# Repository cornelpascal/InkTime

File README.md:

# InkTime

- Cerinta proiectului: https://ocw.cs.pub.ro/courses/tsc/proiect2026
- Portalul de piese JLC mentionat in brief: https://jlcpcb.com/parts

Repository-ul contine schema electrica, PCB-ul, fisierele de manufacturing si ansamblul mecanic pentru un wearable bazat pe nRF52840, cu Bluetooth Low Energy, incarcare prin USB-C, interfata pentru display e-paper, motion sensing, haptic feedback si monitorizare baterie.

## Continutul Repository-ului

- `Hardware/`
  - `WatchSchematic.sch` - schema nativa
  - `WatchSchematic.brd` - layout PCB nativ
  - `WatchSchematic.pdf` / `WatchSchematic1.pdf` - exporturi PDF ale schemei
- `Manufacturing/`
  - `Gerbers.zip` - exporturi Gerber, drill si assembly
  - `bom.csv` - export BOM pentru manufacturing
  - `pick_and_place_top.cpl` - date de plasare pentru fata top
  - `pick_and_place_bottom.cpl` - date de plasare pentru fata bottom
- `Mechanical/`
  - `WatchMechanical.f3z` - assembly Fusion 360
  - `WatchMechanical.step` - export CAD neutru
- `Images/`
  - capturi de render pentru PCB/dispozitiv

## Diagrama Bloc

```text
                         +----------------------+
USB-C -----------------> | USB ESD Protection   |
                         +----------+-----------+
                                    |
                                    v
                         +----------------------+
                         | BQ25180 Charger/PMIC |
                         +----+------------+----+
                              |            |
                              |            +--------------------+
                              v                                 |
                       +-------------+                          |
                       | Li-Po       |                          |
                       | Battery     | --------------------+   |
                       +------+------+                     |   |
                              |                            v   v
                              |                  +----------------------+
                              +----------------> | MAX17048 Fuel Gauge  |
                                                 +----------------------+

                         +----------------------+
                         | RT6160A Buck-Boost   |
                         | 3.3 V Regulator      |
                         +----+----+----+-------+
                              |    |    |
                              |    |    +---------------------> Display E-Paper pe FPC 24 pini
                              |    |
                              |    +-------------------------> DRV2605 Haptic Driver ---> Motor vibratii
                              |
                              +------------------------------> BMA423 IMU
                              |
                              v
                    +-----------------------------------+
                    | nRF52840 BLE + USB MCU            |
                    |                                   |
                    | I2C  -> PMIC / Fuel / IMU / Haptic|
                    | SPI  -> Display E-Paper           |
                    | GPIO -> Butoane / INT / EN        |
                    | USB  -> D+ / D-                   |
                    | SWD  -> Debug Tag-Connect         |
                    +-----+-----------+--------+--------+
                          |           |        |
                          |           |        +--------> Tag-Connect SWD
                          |           +-----------------> 3 butoane user
                          +-----------------------------> Matching Network -> Antena 2.4 GHz
```

## Prezentare Hardware

### Arhitectura principala

- `nRF52840` este controlerul principal. A fost ales deoarece combina BLE, USB, suficienti GPIO, moduri low-power si un ecosistem RF intr-un singur pachet.
- Alimentarea intra prin `USB-C`, trece prin protectia ESD si este gestionata de `BQ25180YBGR`, un charger / PMIC pentru o singura celula.
- Linia de alimentare sustinuta de baterie este reglata de `RT6160AWSC`, un convertor buck-boost care genereaza rail-ul principal `3V3` indiferent de variatia tensiunii bateriei.
- Starea bateriei este masurata de `MAX17048G+T10`.
- Motion sensing este oferit de `BMA423`.
- Haptic feedback este generat de `DRV2605YZFR`, controlat prin I2C si activat printr-un GPIO dedicat.
- Display-ul este conectat printr-un conector `FPC 24 pini, 0.5 mm` si foloseste o magistrala dedicata de tip SPI plus linii de reset/busy/control.
- Semnalul RF de la nRF52840 trece printr-o retea discreta de matching catre o antena chip de 2.4 GHz plasata pe marginea PCB-ului.

### Decizii de design vizibile in implementare

- Toate componentele populate sunt plasate pe fata top; fisierul pick-and-place pentru bottom este gol, conform ghidajului din cerinta.
- Antena RF este pastrata pe marginea placii si separata de zonele dense de cupru, ceea ce respecta cerinta proiectului privind clearance-ul antenei.
- Ceasul foloseste trei butoane hardware pe GPIO-uri dedicate in loc sa le multiplexeze prin display sau PMIC.

## Bill of Materials

BOM-ul complet exportat pentru manufacturing este in [`Manufacturing/bom.csv`](Manufacturing/bom.csv). Tabelul de mai jos listeaza componentele functionale principale, iar coloana `JLC Parts` foloseste fie linkul exact extras din proiect, fie portalul JLC Parts pentru cautarea manuala dupa MPN atunci cand codul JLC nu apare explicit in export.

| Ref | Part | Rol | JLC Parts | Datasheet |
| --- | --- | --- | --- | --- |
| `U1` | nRF52840 | MCU principal BLE/USB | https://jlcpcb.com/partdetail/JLCPCBAssembly-nRF52840/C9900031370 | https://www.nordicsemi.com/-/media/Software-and-other-downloads/Product-Briefs/nRF52840-product-brief.pdf |
| `IC1` | BQ25180YBGR | Charger / PMIC pentru o singura celula | https://jlcpcb.com/partdetail/TexasInstruments-BQ25180YBGR/C3682423 | https://www.ti.com/lit/ds/symlink/bq25180.pdf |
| `IC9` | RT6160AWSC | Regulator buck-boost 3.3 V | https://jlcpcb.com/partdetail/C7065276 | https://www.richtek.com/assets/product_file/RT6160A=RTQ2520A/DS6160A-05.pdf |
| `U3` | MAX17048G+T10 | Fuel gauge pentru baterie | https://jlcpcb.com/partdetail/MaximIntegrated-MAX17048GT10/C2682616 | https://www.analog.com/media/en/technical-documentation/data-sheets/MAX17048-MAX17049.pdf |
| `IC2` | DRV2605YZFR | Driver haptic | https://jlcpcb.com/partdetail/TexasInstruments-DRV2605YZFR/C81079 | https://www.ti.com/lit/ds/symlink/drv2605.pdf |
| `L7` | FTC252012SR47MBCA | Inductor pentru buck-boost | https://jlcpcb.com/partdetail/6763488-FTC252012SR47MBCA/C5832368 | https://product.tdk.com/system/files/dam/doc/product/inductor/inductor/smd/catalog/inductor_commercial_power_mlp2016_en.pdf |
| `IC3` | BMA423 | Accelerometru pe 3 axe | https://jlcpcb.com/parts | https://www.bosch-sensortec.com/media/boschsensortec/downloads/datasheets/bst-bma423-ds000.pdf |
| `ANT1` | 2450AT18B100E | Antena chip 2.4 GHz | https://jlcpcb.com/parts | https://www.johansontechnology.com/datasheets/2450AT18B100.pdf |
| `J1` | Molex 503480-2400 | Conector FPC 24 pini pentru display | https://jlcpcb.com/parts | https://www.molex.com/pdm_docs/sd/5034802400_sd.pdf |
| `J2` | TC2030-IDC | Conector de programare Tag-Connect | https://jlcpcb.com/parts | https://www.tag-connect.com/wp-content/uploads/bsk-pdf-manager/TC2030-IDC-NL.pdf |
| `J4` | KH-TYPE-C-16P | Receptacul USB-C | https://jlcpcb.com/parts | https://atta.szlcsc.com/upload/public/pdf/source/20230720/8A9E0F0B650D1A2FD53D4D542E2F6B37.pdf |
| `D3` | USBLC6-2SC6Y | Protectie ESD pentru USB | https://jlcpcb.com/parts | https://www.st.com/resource/en/datasheet/usblc6-2.pdf |
| `SW_UP`, `SW_ENT`, `SW_DN` | Panasonic EVP-AKE31A | Butoane user | https://jlcpcb.com/parts | https://industry.panasonic.com/cdbs/www-data/pdf/ASQ0000/ASQ0000CE50.pdf |

## Alocare Pini nRF52840

Tabelul urmator documenteaza alocarile efective observate in schema pentru `U1` (`nRF52840`).

| Pin nRF52840 | Net / semnal | Utilizare in design |
| --- | --- | --- |
| `P0.00` | `XL1` | Terminal cristal LF 32.768 kHz |
| `P0.01` | `XL2` | Terminal cristal LF 32.768 kHz |
| `P0.02` | `SCK` | SPI clock pentru display-ul e-paper |
| `P0.03` | `MOSI` | SPI MOSI pentru display-ul e-paper |
| `P0.05` | `EPD_CS` | Chip select pentru display |
| `P0.06` | `SDA` | I2C SDA comun pentru PMIC, fuel gauge, haptic si alte periferice I2C |
| `P0.07` | `SCL` | I2C SCL comun pentru PMIC, fuel gauge, haptic si alte periferice I2C |
| `P0.08` | `IMU_INT1` | Intrerupere principala de la `BMA423` |
| `P0.10` | `ALERT` | Semnal `ALERT` de la `MAX17048` |
| `P0.11` | `PMIC_INT` | Intrerupere de la `BQ25180` |
| `P0.12` | `HAPTIC_EN` | Enable pentru `DRV2605` |
| `P0.13` | `P0.13` | Intrare buton `SW_UP` |
| `P0.14` | `P0.14` | Intrare buton `SW_ENT` |
| `P0.15` | `EPD_DC` | Linia data/command pentru display |
| `P0.16` | `EPD_RST` | Reset hardware pentru display |
| `P0.17` | `EPD_BUSY` | Busy/status de la display |
| `P0.18` | `RESET` | Reset extern, dus si la Tag-Connect (`J2`) |
| `P1.00` | `SWO` | Optional trace / debug output pe test pad |
| `P1.02` | `P1.02` | Intrare buton `SW_DN` |
| `P1.08` | `IMU_INT2` | A doua intrerupere de la `BMA423` |
| `SWDIO` | `SWDIO` | Debug/programare prin `J2` |
| `SWDCLK` | `SWDCLK` | Clock debug/programare prin `J2` |
| `D-` | `D-` | USB FS data minus de la conectorul USB-C, prin protectia ESD |
| `D+` | `D+` | USB FS data plus de la conectorul USB-C, prin protectia ESD |
| `VBUS` | `VBUS` | Detectie/alimentare USB venita din conectorul USB-C |

Pinii `P0.04`, `P0.09`, `P1.01`, `P1.03`-`P1.07`, `P1.09`-`P1.15` si `P0.19`-`P0.31` apar in simbolul MCU, dar in schema curenta nu au o functie periferica documentata explicit; pot ramane disponibili pentru extensii sau pentru iteratii viitoare ale designului.

## Fisiere de Manufacturing

Artefactele prezente in acest repository:

- Arhiva Gerber: [`Manufacturing/Gerbers.zip`](Manufacturing/Gerbers.zip)
- Datele de drill incluse in arhiva
- Fisiere de assembly placement:
  - [`Manufacturing/pick_and_place_top.cpl`](Manufacturing/pick_and_place_top.cpl)
  - [`Manufacturing/pick_and_place_bottom.cpl`](Manufacturing/pick_and_place_bottom.cpl)
- Export BOM: [`Manufacturing/bom.csv`](Manufacturing/bom.csv)

Arhiva Gerber curenta contine fisiere pentru top/bottom copper, soldermask, silkscreen, solderpaste, drill si profile. Fisierul de plasare pentru top este populat; fisierul de plasare pentru bottom este gol, ceea ce este consistent cu o strategie de asamblare doar pe fata top.

## Livrabile Mecanice

- Ansamblu Fusion: [`Mechanical/WatchMechanical.f3z`](Mechanical/WatchMechanical.f3z)
- Export STEP: [`Mechanical/WatchMechanical.step`](Mechanical/WatchMechanical.step)

Aceste fisiere sunt destinate validarii potrivirii carcasei pentru PCB, baterie, stack-ul display-ului si alinierea conectorilor/butoanelor ceruta de proiect.

## Imagini Render

## Note de Implementare

- Designul urmeaza structura ceruta de proiect pentru `Hardware`, `Manufacturing`, `Mechanical`, `Images`, `LICENSE` si `README.md`.
- PCB-ul este o placa compacta pentru wearable, cu functii RF, power, sensing, haptics, display, USB si debug integrate intr-un singur design.
- Arhitectura aleasa minimizeaza modulele externe prin integrarea directa pe placa a functiilor de charging, regulation, sensing, battery monitoring si control haptic.
- Zonele cele mai sensibile la rutare sunt traseul RF, regiunea perechii diferentiale USB, zona de conversie de putere si sectiunea densa a conectorului de display.

## Aliniere cu Checklist-ul de Review

Acest README a fost scris pentru a acoperi documentatia necesara:

- diagrama bloc
- BOM cu linkuri de procurement si datasheet
- functionalitate hardware detaliata
- utilizarea explicita a pinilor nRF52840
- note de implementare utile in timpul review-ului
- linkuri catre schema, PCB-ul, fisierele de manufacturing si artefactele mecanice livrate

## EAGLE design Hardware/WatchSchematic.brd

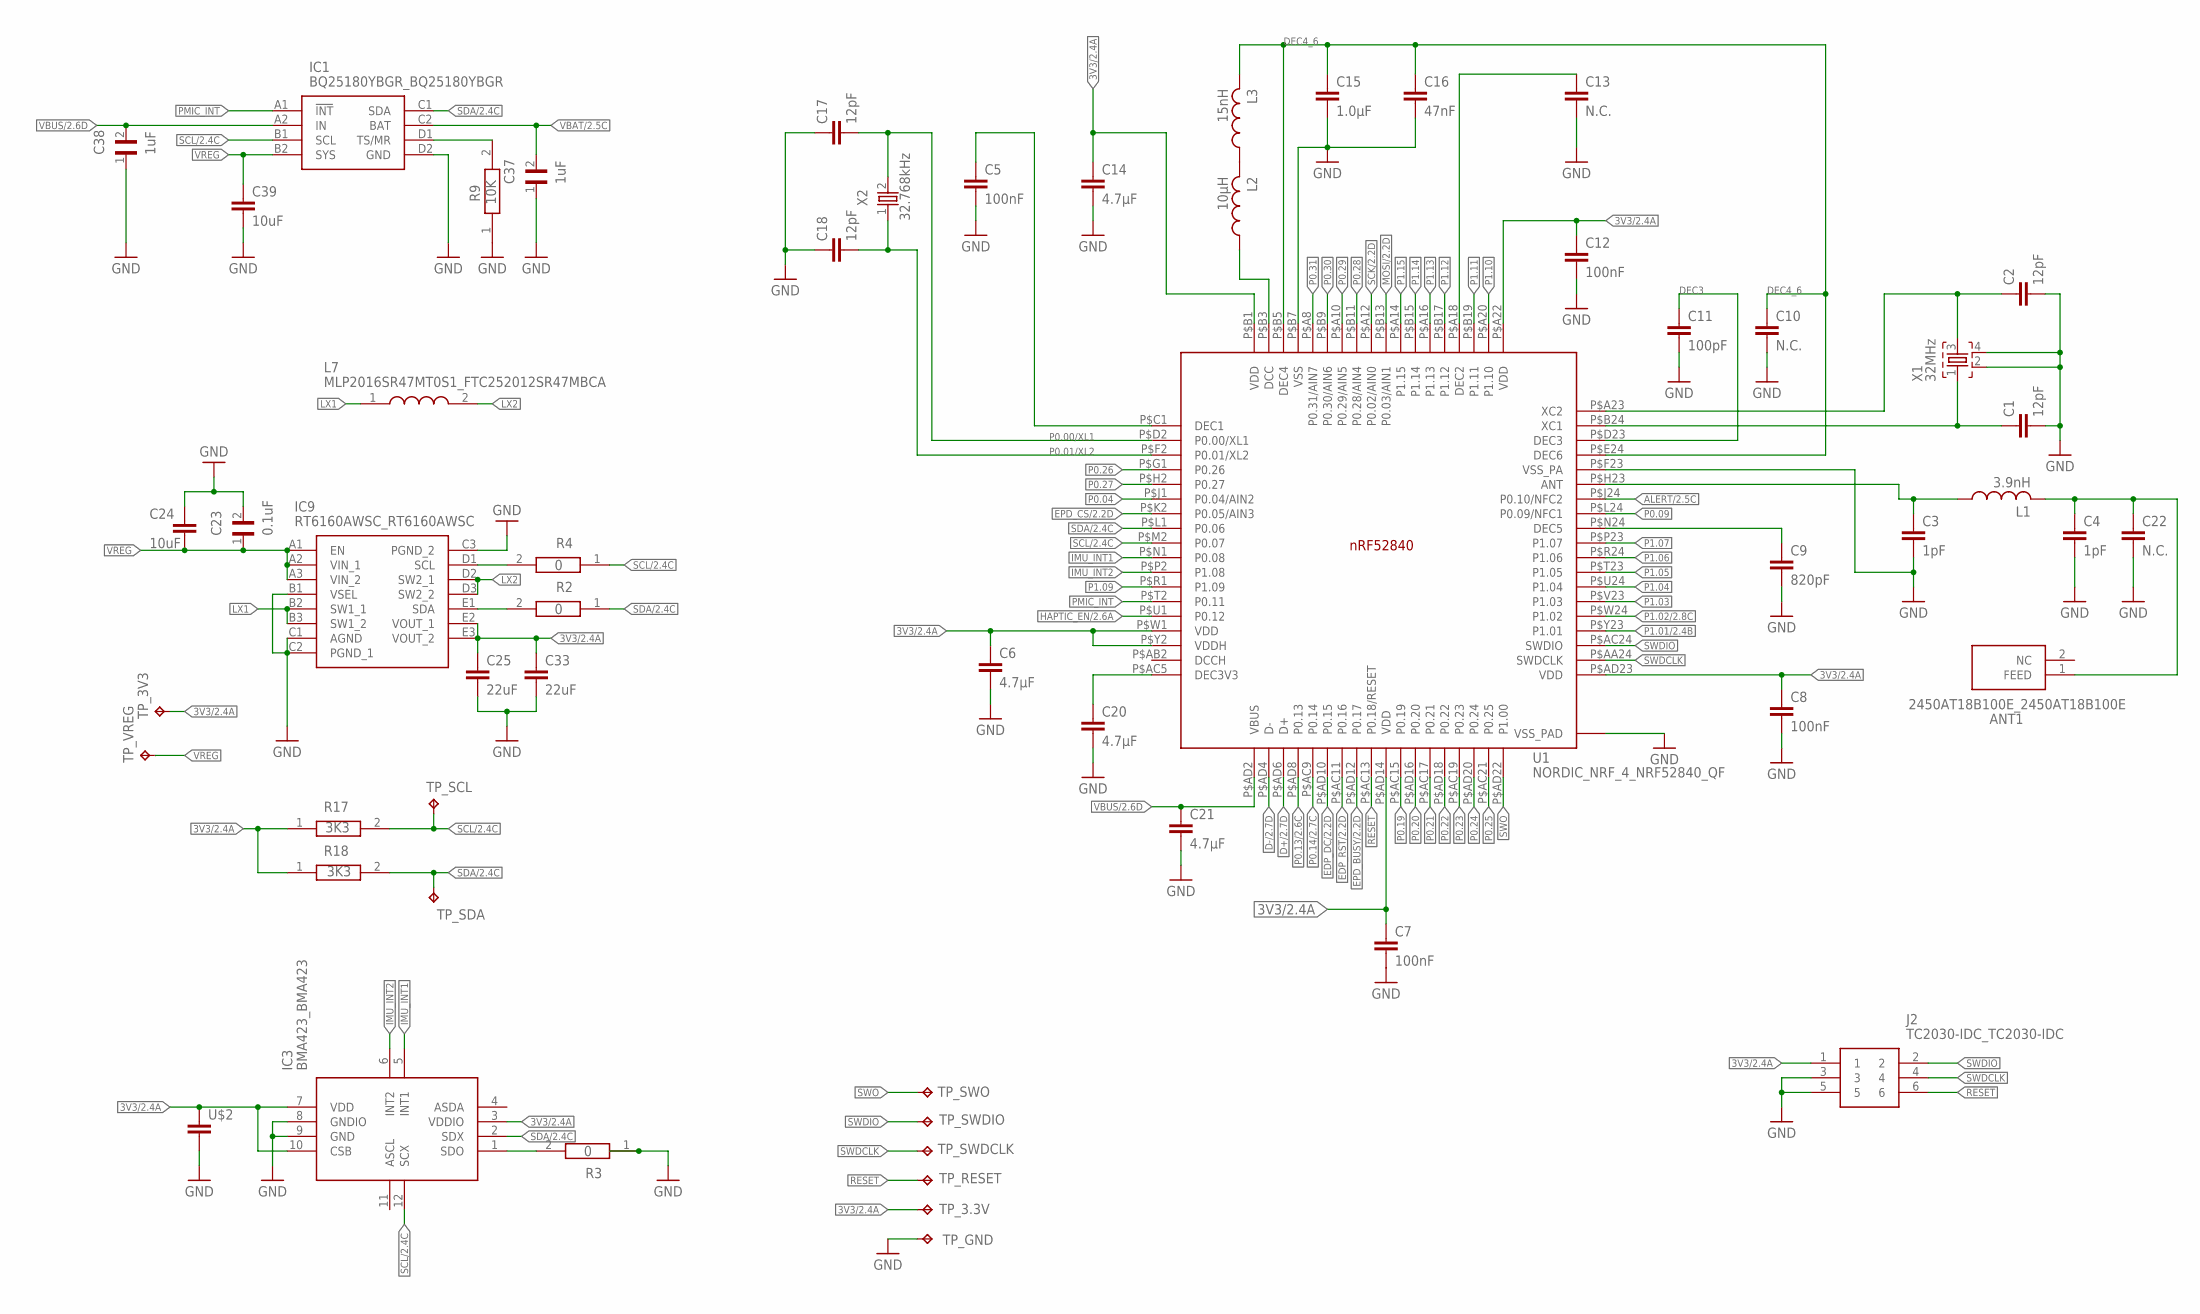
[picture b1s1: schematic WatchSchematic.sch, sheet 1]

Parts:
ANT1: 2450AT18B100E_2450AT18B100E; 2450AT18B100E_ANTC3216X140N
C1, C2, C17, C18: 12pF; NORDIC_NRF_3_RESC0201_L
C3, C4: 1pF; NORDIC_NRF_3_RESC0201_L
C5, C7, C8, C12: 100nF; NORDIC_NRF_3_RESC0201_L
C6, C14, C20, C21: 4.7μF; NORDIC_NRF_3_RESC0201_L
C9: 820pF; NORDIC_NRF_3_RESC0201_L
C10, C13, C22: N.C.; NORDIC_NRF_3_RESC0201_L
C11: 100pF; NORDIC_NRF_3_RESC0201_L
C15: 1.0μF; NORDIC_NRF_3_RESC0201_L
C16: 47nF; NORDIC_NRF_3_RESC0201_L
C23: 0.1uF; GRM011R60J152KE01L_1_0201
C24, C39: 10uF; NORDIC_NRF_3_RESC0201_L
C25, C33: 22uF; NORDIC_NRF_3_RESC0201_L
C37, C38: 1uF; GRM011R60J152KE01L_1_0201
IC1: BQ25180YBGR_BQ25180YBGR; BQ25180YBGR_BGA8C40P2X4_100X155X50
IC3: BMA423_BMA423
IC9: RT6160AWSC_RT6160AWSC; RT6160AWSC_BGA15C40P3X5_140X230X60
J2: TC2030-IDC_TC2030-IDC; TC2030-IDC_TC2030IDC
L1: 3.9nH; NORDIC_NRF_2_RESC0402_L
L2: 10μH; NORDIC_NRF_2_RESC0402_L
L3: 15nH; NORDIC_NRF_2_RESC0402_L
L7: MLP2016SR47MT0S1_FTC252012SR47MBCA; MLP2016SR47MT0S1_INDC2016X100N
R2, R3, R4: 0; CPF0201D7K68C1_0201
R9: 10K; CPF0201D7K68C1_0201
R17, R18: 3K3; CPF0201D7K68C1_0201
TP_3.3V, TP_3V3: HECTOR_WATCH_1_TPTP20R; HECTOR_WATCH_1_TP20R
TP_GND: HECTOR_WATCH_1_TPTP20R; HECTOR_WATCH_1_TP20R
TP_RESET: HECTOR_WATCH_1_TPTP20R; HECTOR_WATCH_1_TP20R
TP_SCL: HECTOR_WATCH_1_TPTP20R; HECTOR_WATCH_1_TP20R
TP_SDA: HECTOR_WATCH_1_TPTP20R; HECTOR_WATCH_1_TP20R
TP_SWDCLK: HECTOR_WATCH_1_TPTP20R; HECTOR_WATCH_1_TP20R
TP_SWDIO: HECTOR_WATCH_1_TPTP20R; HECTOR_WATCH_1_TP20R
TP_SWO: HECTOR_WATCH_1_TPTP20R; HECTOR_WATCH_1_TP20R
TP_VREG: HECTOR_WATCH_1_TPTP20R; HECTOR_WATCH_1_TP20R
U1: NORDIC_NRF_4_NRF52840_QF; NORDIC_NRF_4_AQFN50P700X700X85_HS-74N
U$2: NORDIC_NRF_3_CAPACITOR_0201_L; NORDIC_NRF_3_RESC0201_L
X1: 32MHz; NORDIC_NRF_BT-XTAL_2016_N
X2: 32.768kHz; NORDIC_NRF_1_XTAL_3215_N

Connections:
3V3/2.4A: C6.1, C7.1, C8.1, C12.1, C14.1, C25.1, C33.1, IC3.3 (VDDIO), IC3.7 (VDD), IC3.10 (CSB), IC9.E2 (VOUT_1), IC9.E3 (VOUT_2), J2.1, R17.1, R18.1, TP_3.3V.TP, TP_3V3.TP, U1.P$A22 (VDD), U1.P$AD14 (VDD), U1.P$AD23 (VDD), U1.P$B1 (VDD), U1.P$W1 (VDD), U1.P$Y2 (VDDH), U$2.1
ALERT/2.5C: U1.P$J24 (P0.10/NFC2)
D+/2.7D: U1.P$AD6 (D+)
D-/2.7D: U1.P$AD4 (D-)
DEC3: C11.1, U1.P$D23 (DEC3)
DEC4_6: C10.1, C15.1, C16.1, L3.2, U1.P$B5 (DEC4), U1.P$E24 (DEC6)
EDP_DC/2.2D: U1.P$AD10 (P0.15)
EDP_RST/2.2D: U1.P$AC11 (P0.16)
EPD_BUSY/2.2D: U1.P$AD12 (P0.17)
EPD_CS/2.2D: U1.P$K2 (P0.05/AIN3)
GND: C1.2, C2.2, C3.2, C4.2, C5.2, C6.2, C7.2, C8.2, C9.2, C10.2, C11.2, C12.2, C13.2, C14.2, C15.2, C16.2, C17.1, C18.1, C20.2, C21.2, C22.2, C23.2, C24.1, C25.2, C33.2, C37.1, C38.1, C39.2, IC1.D2 (GND), IC3.8 (GNDIO), IC3.9 (GND), IC9.B1 (VSEL), IC9.C1 (AGND), IC9.C2 (PGND_1), IC9.C3 (PGND_2), J2.3, J2.5, R3.1, R9.1, TP_GND.TP, U1.P$74 (VSS_PAD), U1.P$75 (VSS_PAD), U1.P$76 (VSS_PAD), U1.P$77 (VSS_PAD), U1.P$78 (VSS_PAD), U1.P$79 (VSS_PAD), U1.P$80 (VSS_PAD), U1.P$81 (VSS_PAD), U1.P$82 (VSS_PAD), U1.P$83 (VSS_PAD), U1.P$84 (VSS_PAD), U1.P$85 (VSS_PAD), U1.P$86 (VSS_PAD), U1.P$87 (VSS_PAD), U1.P$88 (VSS_PAD), U1.P$89 (VSS_PAD), U1.P$90 (VSS_PAD), U1.P$B7 (VSS), U1.P$F23 (VSS_PA), U$2.2, X1.2, X1.4; also elsewhere on the board
HAPTIC_EN/2.6A: U1.P$U1 (P0.12)
IMU_INT1: IC3.5 (INT1), U1.P$N1 (P0.08)
IMU_INT2: IC3.6 (INT2), U1.P$P2 (P1.08)
LX1: IC9.B2 (SW1_1), IC9.B3 (SW1_2), L7.1
LX2: IC9.D2 (SW2_1), IC9.D3 (SW2_2), L7.2
MOSI/2.2D: U1.P$B13 (P0.03/AIN1)
unnamed: IC9.E1 (SDA), R2.2
unnamed: IC1.D1 (TS/MR), R9.2
unnamed: C5.1, U1.P$C1 (DEC1)
unnamed: IC3.1 (SDO), R3.2
unnamed: L2.2, L3.1
unnamed: L2.1, U1.P$B3 (DCC)
unnamed: IC9.D1 (SCL), R4.2
unnamed: C13.1, U1.P$A18 (DEC2)
unnamed: C1.1, U1.P$B24 (XC1), X1.1
unnamed: C2.1, U1.P$A23 (XC2), X1.3
unnamed: C9.1, U1.P$N24 (DEC5)
unnamed: C3.1, L1.1, U1.P$H23 (ANT)
unnamed: ANT1.1 (FEED), C4.1, C22.1, L1.2
unnamed: C20.1, U1.P$AC5 (DEC3V3)
P0.00/XL1: C17.2, U1.P$D2 (P0.00/XL1), X2.2
P0.01/XL2: C18.2, U1.P$F2 (P0.01/XL2), X2.1
P0.04: U1.P$J1 (P0.04/AIN2)
P0.09: U1.P$L24 (P0.09/NFC1)
P0.13/2.6C: U1.P$AD8 (P0.13)
P0.14/2.7C: U1.P$AC9 (P0.14)
P0.19: U1.P$AC15 (P0.19)
P0.20: U1.P$AD16 (P0.20)
P0.21: U1.P$AC17 (P0.21)
P0.22: U1.P$AD18 (P0.22)
P0.23: U1.P$AC19 (P0.23)
P0.24: U1.P$AD20 (P0.24)
P0.25: U1.P$AC21 (P0.25)
P0.26: U1.P$G1 (P0.26)
P0.27: U1.P$H2 (P0.27)
P0.28: U1.P$B11 (P0.28/AIN4)
P0.29: U1.P$A10 (P0.29/AIN5)
P0.30: U1.P$B9 (P0.30/AIN6)
P0.31: U1.P$A8 (P0.31/AIN7)
P1.01/2.4B: U1.P$Y23 (P1.01)
P1.02/2.8C: U1.P$W24 (P1.02)
P1.03: U1.P$V23 (P1.03)
P1.04: U1.P$U24 (P1.04)
P1.05: U1.P$T23 (P1.05)
P1.06: U1.P$R24 (P1.06)
P1.07: U1.P$P23 (P1.07)
P1.09: U1.P$R1 (P1.09)
P1.10: U1.P$A20 (P1.10)
P1.11: U1.P$B19 (P1.11)
P1.12: U1.P$B17 (P1.12)
P1.13: U1.P$A16 (P1.13)
P1.14: U1.P$B15 (P1.14)
P1.15: U1.P$A14 (P1.15)
PMIC_INT: IC1.A1 (!INT), U1.P$T2 (P0.11)
RESET: J2.6, TP_RESET.TP, U1.P$AC13 (P0.18/RESET)
SCK/2.2D: U1.P$A12 (P0.02/AIN0)
SCL/2.4C: IC1.B1 (SCL), IC3.12 (SCX), R4.1, R17.2, TP_SCL.TP, U1.P$M2 (P0.07)
SDA/2.4C: IC1.C1 (SDA), IC3.2 (SDX), R2.1, R18.2, TP_SDA.TP, U1.P$L1 (P0.06)
SWDCLK: J2.4, TP_SWDCLK.TP, U1.P$AA24 (SWDCLK)
SWDIO: J2.2, TP_SWDIO.TP, U1.P$AC24 (SWDIO)
SWO: TP_SWO.TP, U1.P$AD22 (P1.00)
VBAT/2.5C: C37.2, IC1.C2 (BAT)
VBUS/2.6D: C21.1, C38.2, IC1.A2 (IN), U1.P$AD2 (VBUS)
VREG: C23.1, C24.2, C39.1, IC1.B2 (SYS), IC9.A1 (EN), IC9.A2 (VIN_1), IC9.A3 (VIN_2), TP_VREG.TP

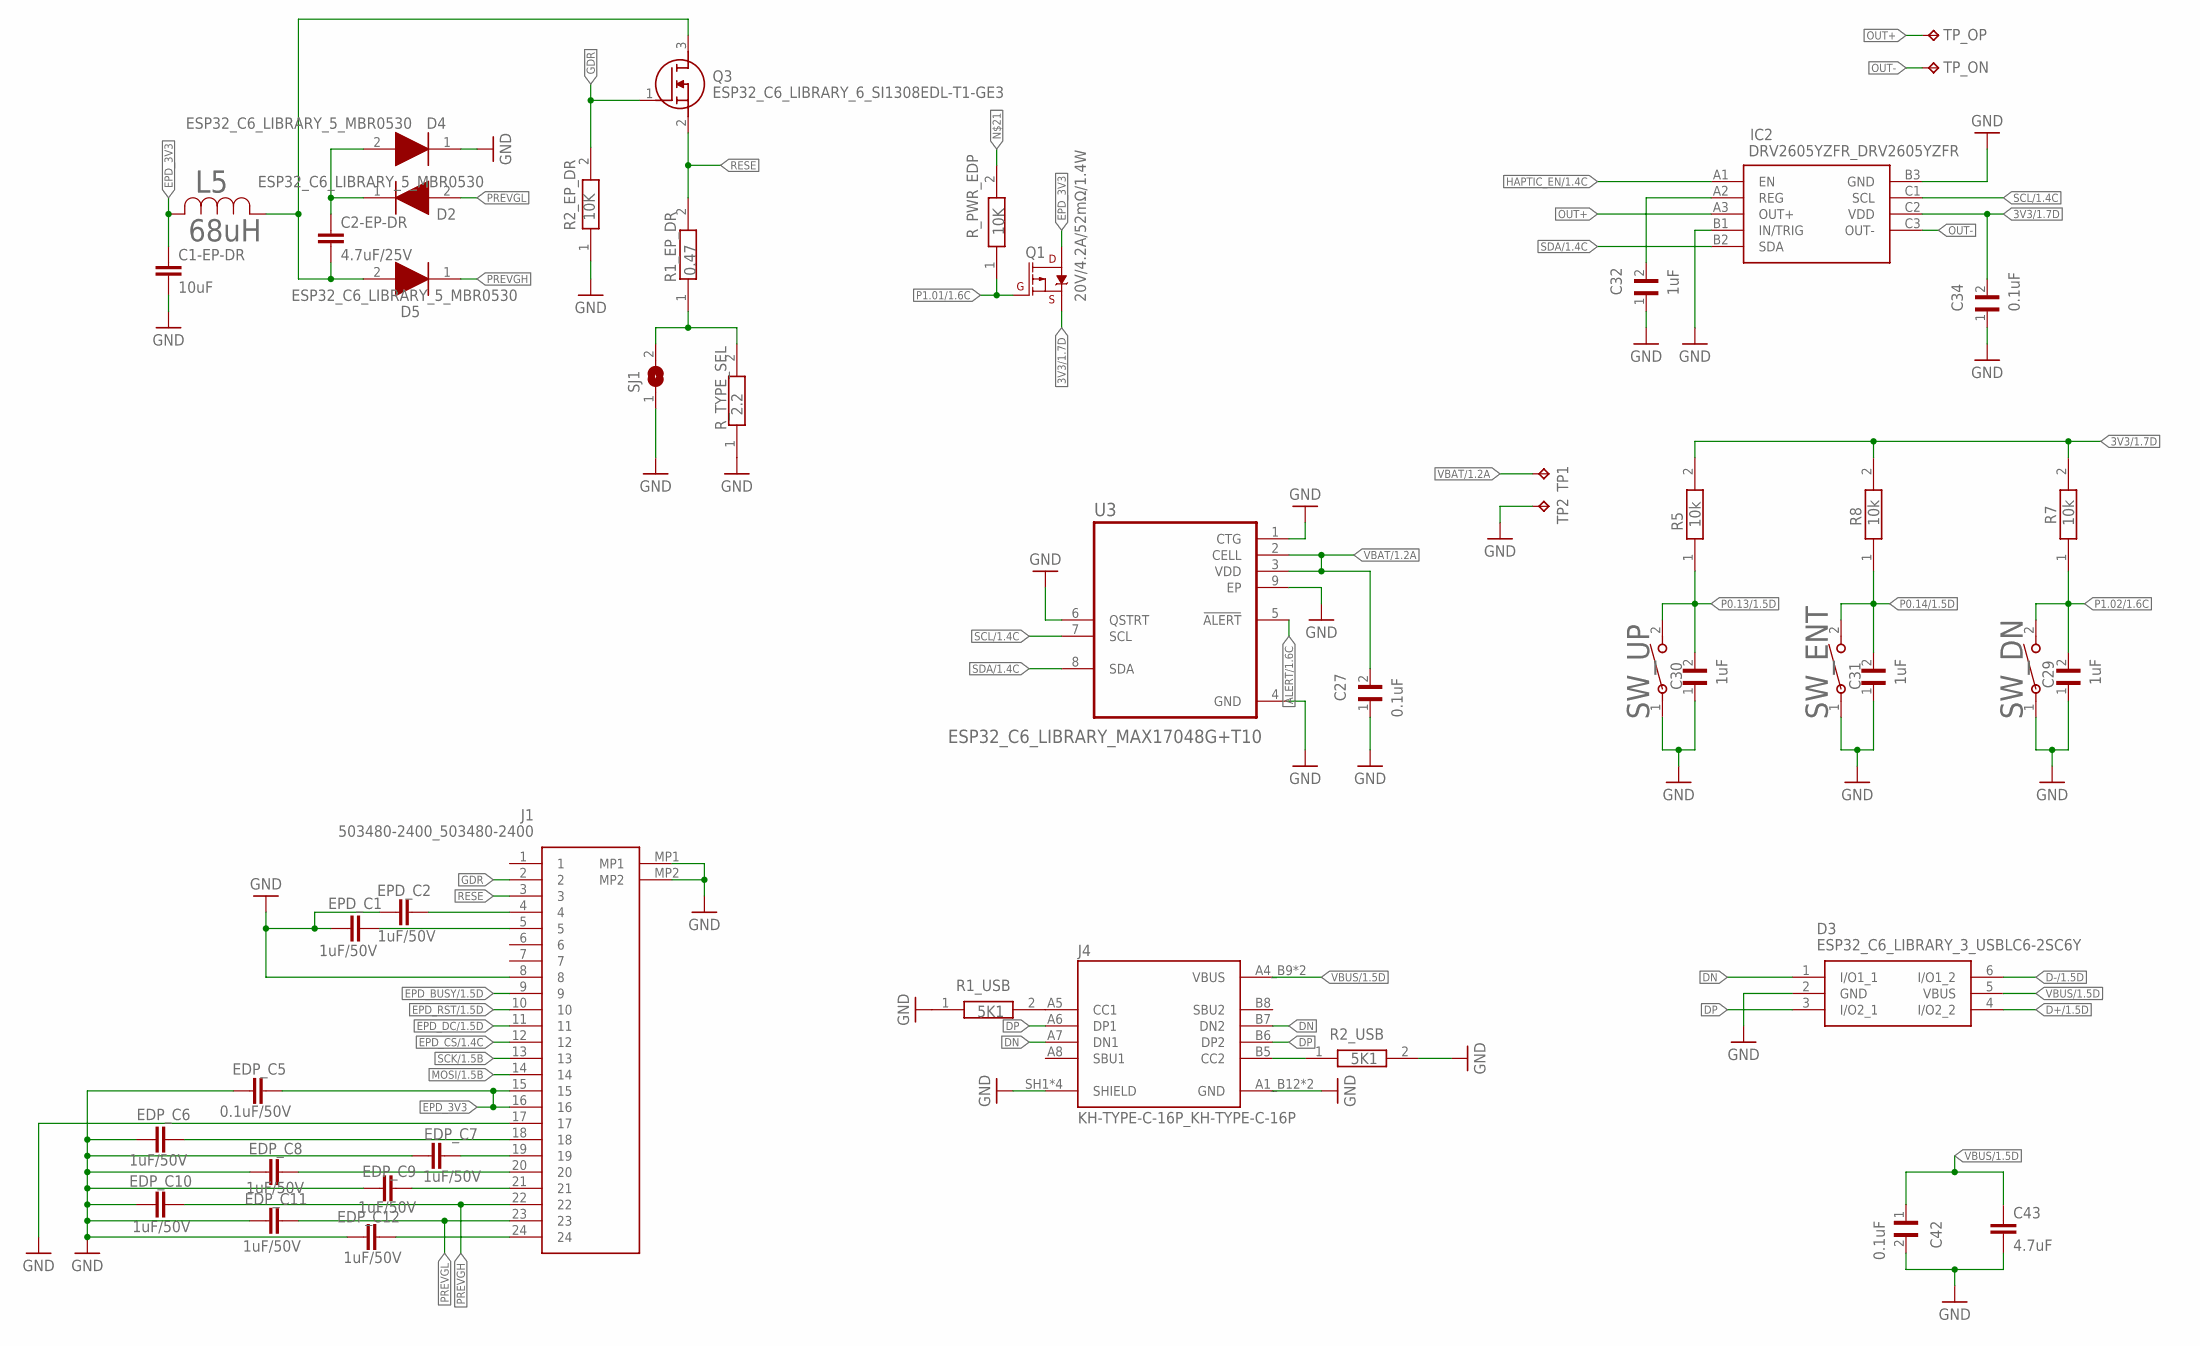
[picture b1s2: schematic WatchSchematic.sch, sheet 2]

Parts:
C1-EP-DR: 10uF; NORDIC_NRF_3_RESC0201_L
C2-EP-DR: 4.7uF/25V; NORDIC_NRF_3_RESC0201_L
C27, C34, C42: 0.1uF; GRM011R60J152KE01L_1_0201
C29, C30, C31, C32: 1uF; GRM011R60J152KE01L_1_0201
C43: 4.7uF; NORDIC_NRF_3_RESC0201_L
D2, D4, D5: ESP32_C6_LIBRARY_5_MBR0530; ESP32_C6_LIBRARY_5_SOD3716X135N
D3: ESP32_C6_LIBRARY_3_USBLC6-2SC6Y; ESP32_C6_LIBRARY_3_SOT95P280X145-6N
EDP_C5: 0.1uF/50V; NORDIC_NRF_3_RESC0201_L
EDP_C6, EDP_C7, EDP_C8, EDP_C9, EDP_C10, EDP_C11, EDP_C12: 1uF/50V; NORDIC_NRF_3_RESC0201_L
EPD_C1, EPD_C2: 1uF/50V; NORDIC_NRF_3_RESC0201_L
IC2: DRV2605YZFR_DRV2605YZFR; DRV2605YZFR_BGA9C50P3X3_144X144X62
J1: 503480-2400_503480-2400; 503480-2400_5034802400
J4: KH-TYPE-C-16P_KH-TYPE-C-16P; KH-TYPE-C-16P_KINGHELM_KH-TYPE-C-16P
L5: 68uH; ESP32_C6_LIBRARY_2_IND_4828-WE-TPC_WRE
Q1: 20V/4.2A/52mΩ/1.4W; ESP32_C6_LIBRARY_4_ESP32_C6_LIBRARY_4_ESP32_C6_LIBRARY_4_ES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
Q3: ESP32_C6_LIBRARY_6_SI1308EDL-T1-GE3; ESP32_C6_LIBRARY_6_SOT65P210X110-3N
R1_EP_DR: 0.47; CPF0201D7K68C1_0201
R1_USB, R2_USB: 5K1; CPF0201D7K68C1_0201
R2_EP_DR: 10K; CPF0201D7K68C1_0201
R5, R7, R8: 10k; CPF0201D7K68C1_0201
R_PWR_EDP: 10K; CPF0201D7K68C1_0201
R_TYPE_SEL: 2.2; CPF0201D7K68C1_0201
SJ1: ESP32_C6_LIBRARY_7_JUMPER_SJ
SW_DN: 2025-10-22_07-23-44_LIBRARY_EVP-AKE31ASW_EVP-AKE3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; 2025-10-22_07-23-44_LIBRARY_SW_EVP-AKE31A_PAN
SW_ENT: 2025-10-22_07-23-44_LIBRARY_EVP-AKE31ASW_EVP-AKE3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; 2025-10-22_07-23-44_LIBRARY_SW_EVP-AKE31A_PAN
SW_UP: 2025-10-22_07-23-44_LIBRARY_EVP-AKE31ASW_EVP-AKE3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; 2025-10-22_07-23-44_LIBRARY_SW_EVP-AKE31A_PAN
TP1, TP2: HECTOR_WATCH_1_TPTP20R; HECTOR_WATCH_1_TP20R
TP_ON: HECTOR_WATCH_1_TPTP20R; HECTOR_WATCH_1_TP20R
TP_OP: HECTOR_WATCH_1_TPTP20R; HECTOR_WATCH_1_TP20R
U3: ESP32_C6_LIBRARY_MAX17048G+T10; ESP32_C6_LIBRARY_SON50P200X200X80-9N

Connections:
3V3/1.7D: C34.2, IC2.C2 (VDD), Q1.2 (S), R5.2, R7.2, R8.2
ALERT/1.6C: U3.5 (!ALERT)
D+/1.5D: D3.4 (I/O2_2)
D-/1.5D: D3.6 (I/O1_2)
DN: D3.1 (I/O1_1), J4.A7 (DN1), J4.B7 (DN2)
DP: D3.3 (I/O2_1), J4.A6 (DP1), J4.B6 (DP2)
EPD_3V3: C1-EP-DR.1, EDP_C5.2, J1.15, J1.16, L5.2, Q1.3 (D)
EPD_BUSY/1.5D: J1.9
EPD_CS/1.4C: J1.12
EPD_DC/1.5D: J1.11
EPD_RST/1.5D: J1.10
GDR: J1.2, Q3.1 (G), R2_EP_DR.2
GND: C1-EP-DR.2, C27.1, C29.1, C30.1, C31.1, C32.1, C34.1, C42.2, C43.2, D3.2 (GND), D4.1 (K), EDP_C5.1, EDP_C6.1, EDP_C7.1, EDP_C8.1, EDP_C9.1, EDP_C10.1, EDP_C11.1, EDP_C12.1, EPD_C1.1, EPD_C2.1, IC2.B1 (IN/TRIG), IC2.B3 (GND), J1.8, J1.17, J1.MP1, J1.MP2, J4.A1_B12 (GND), J4.A12_B1 (GND), J4.SH1 (SHIELD), J4.SH2 (SHIELD), J4.SH3 (SHIELD), J4.SH4 (SHIELD), R1_USB.1, R2_EP_DR.1, R2_USB.2, R_TYPE_SEL.1, SJ1.1, SW_DN.1, SW_ENT.1, SW_UP.1, TP2.TP, U3.1 (CTG), U3.4 (GND), U3.6 (QSTRT), U3.9 (EP); also elsewhere on the board
HAPTIC_EN/1.4C: IC2.A1 (EN)
MOSI/1.5B: J1.14
unnamed: J4.A5 (CC1), R1_USB.2
unnamed: C2-EP-DR.2, D5.2 (A), L5.1, Q3.3 (D)
unnamed: C2-EP-DR.1, D2.1 (K), D4.2 (A)
unnamed: EPD_C2.2, J1.4
unnamed: EPD_C1.2, J1.5
unnamed: R1_EP_DR.1, R_TYPE_SEL.2, SJ1.2
unnamed: C32.2, IC2.A2 (REG)
unnamed: EDP_C7.2, J1.19
unnamed: EDP_C6.2, J1.18
unnamed: EDP_C8.2, J1.20
unnamed: EDP_C9.2, J1.21
unnamed: EDP_C12.2, J1.24
unnamed: J4.B5 (CC2), R2_USB.1
OUT+: IC2.A3 (OUT+), TP_OP.TP
OUT-: IC2.C3 (OUT-), TP_ON.TP
P0.13/1.5D: C30.2, R5.1, SW_UP.2
P0.14/1.5D: C31.2, R8.1, SW_ENT.2
P1.01/1.6C: Q1.1 (G), R_PWR_EDP.1
P1.02/1.6C: C29.2, R7.1, SW_DN.2
PREVGH: D5.1 (K), EDP_C10.2, J1.22
PREVGL: D2.2 (A), EDP_C11.2, J1.23
RESE: J1.3, Q3.2 (S), R1_EP_DR.2
SCK/1.5B: J1.13
SCL/1.4C: IC2.C1 (SCL), U3.7 (SCL)
SDA/1.4C: IC2.B2 (SDA), U3.8 (SDA)
VBAT/1.2A: C27.2, TP1.TP, U3.2 (CELL), U3.3 (VDD)
VBUS/1.5D: C42.1, C43.1, D3.5 (VBUS), J4.A4_B9 (VBUS), J4.A9_B4 (VBUS)

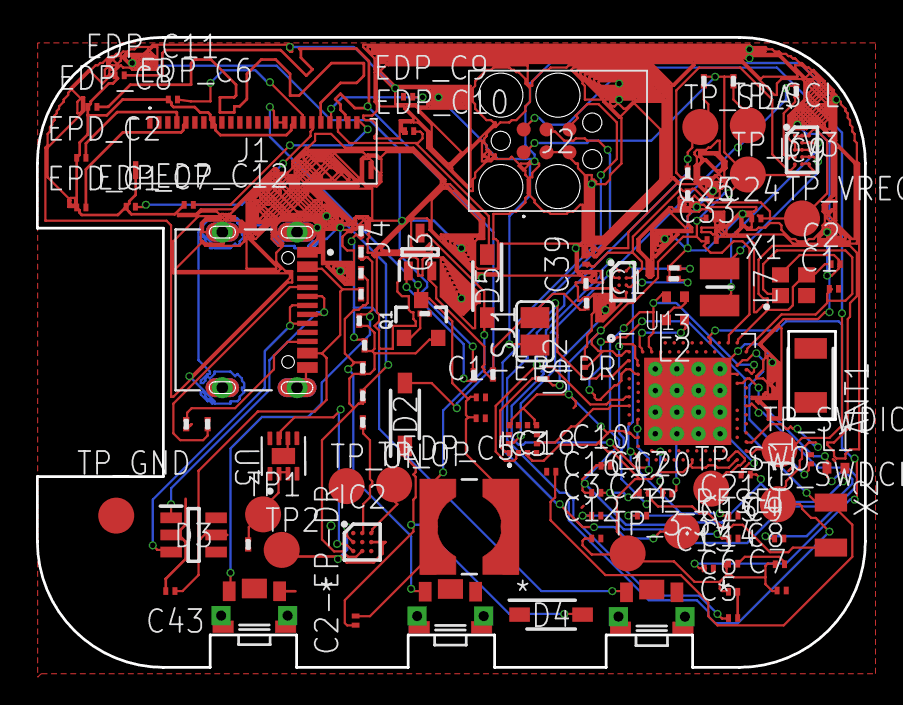
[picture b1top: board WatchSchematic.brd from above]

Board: 2 copper layers, 46.0 x 35.0 mm, 105 parts (0 on the bottom side), 65 nets.

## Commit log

2026-04-08 + schematic files EVT
2026-04-09 + PCB layout EVT
2026-04-20 all done
2026-04-21 solved issues
2026-04-21 final issues solved

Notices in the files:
parts and their libraries:
COPYRIGHT: Copyright (C) 2024 Ultra Librarian. All rights reserved.
COPYRIGHT: Copyright (C) 2025 Ultra Librarian. All rights reserved.
